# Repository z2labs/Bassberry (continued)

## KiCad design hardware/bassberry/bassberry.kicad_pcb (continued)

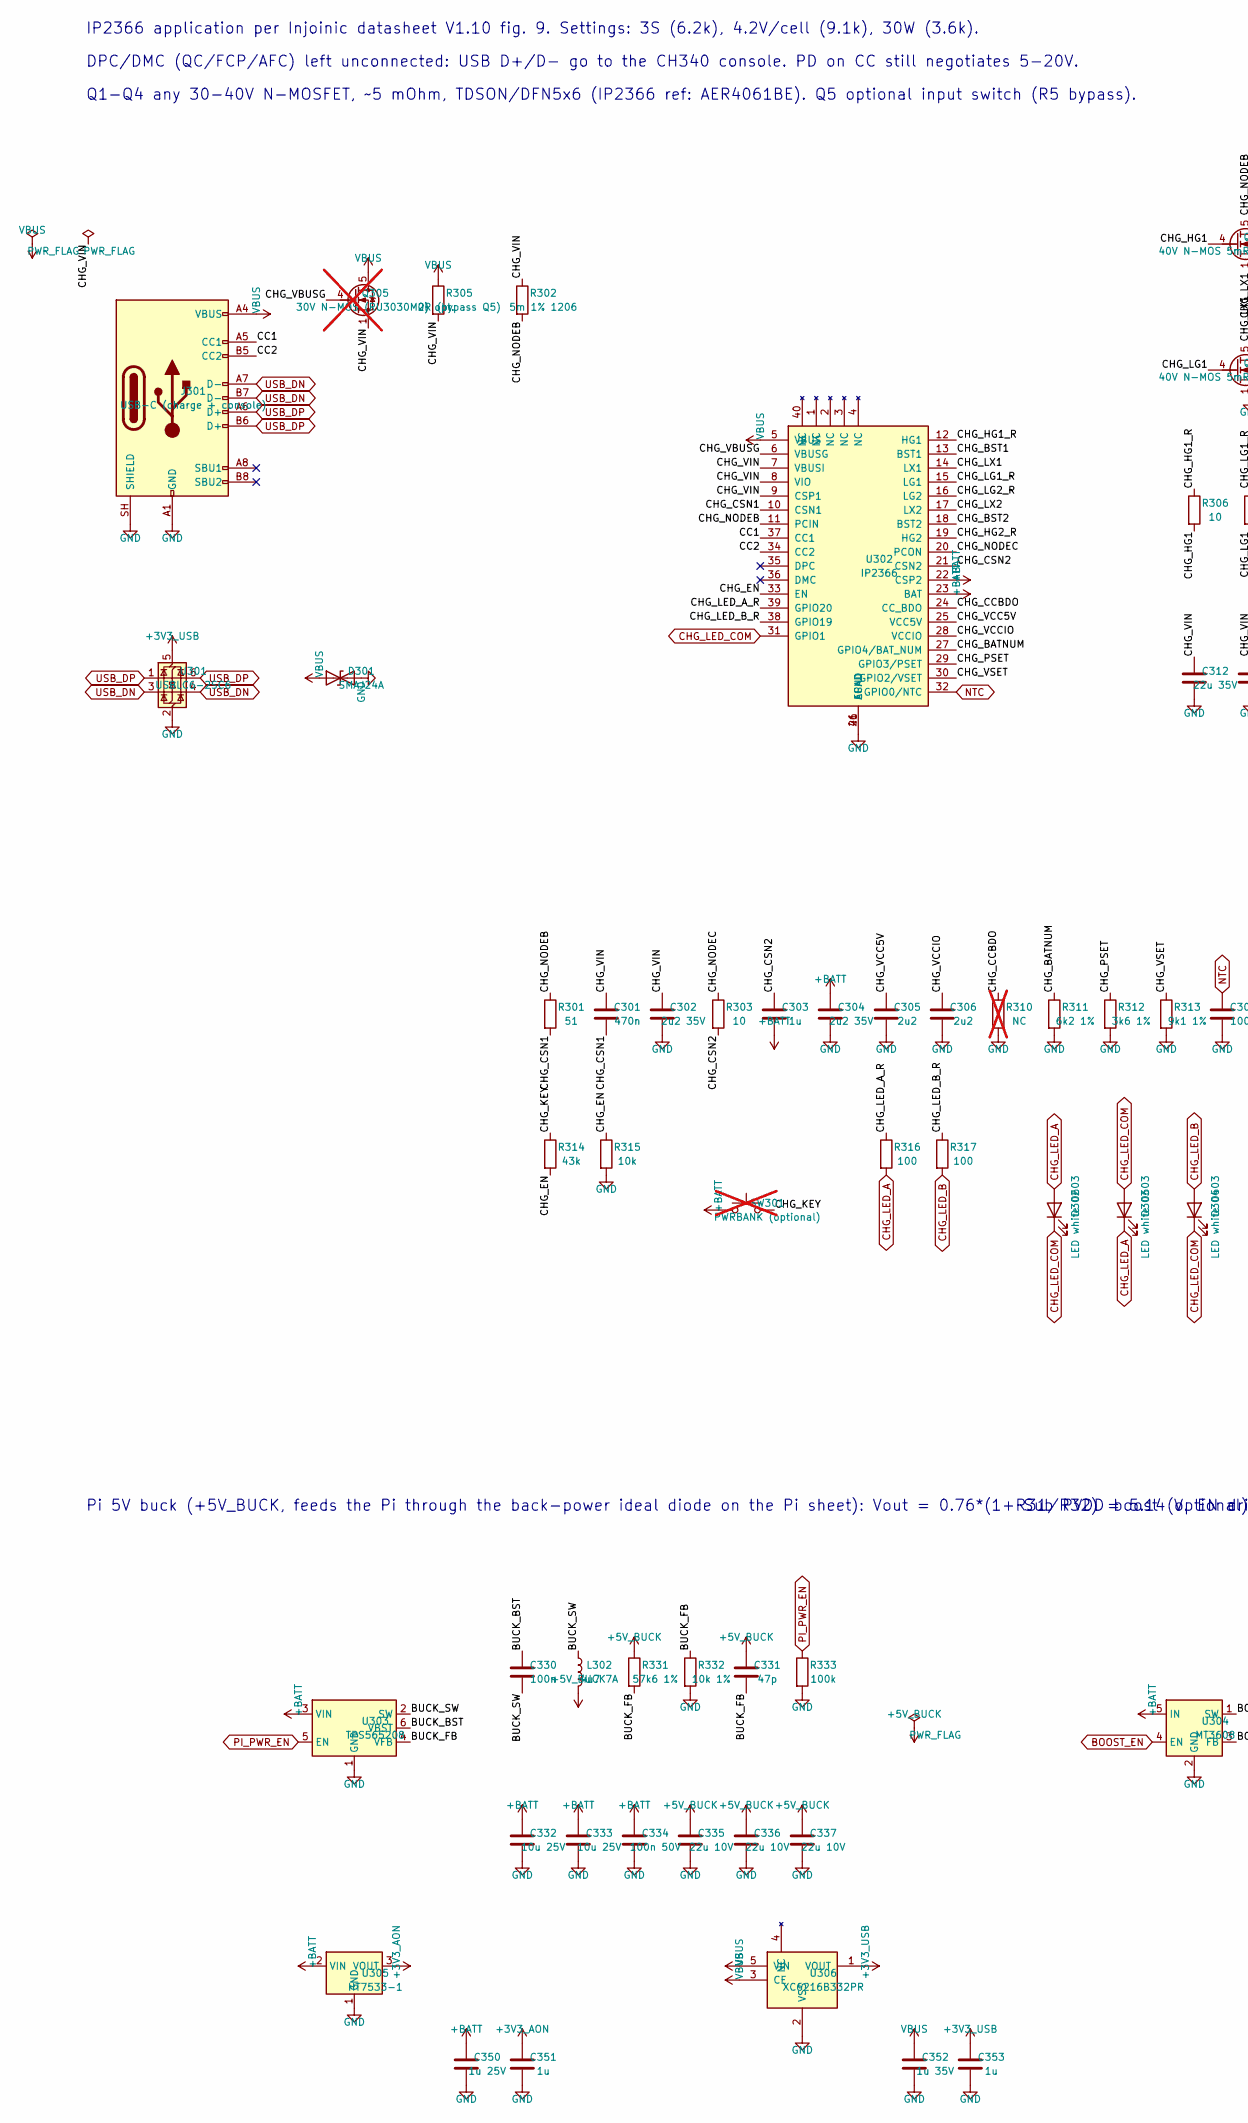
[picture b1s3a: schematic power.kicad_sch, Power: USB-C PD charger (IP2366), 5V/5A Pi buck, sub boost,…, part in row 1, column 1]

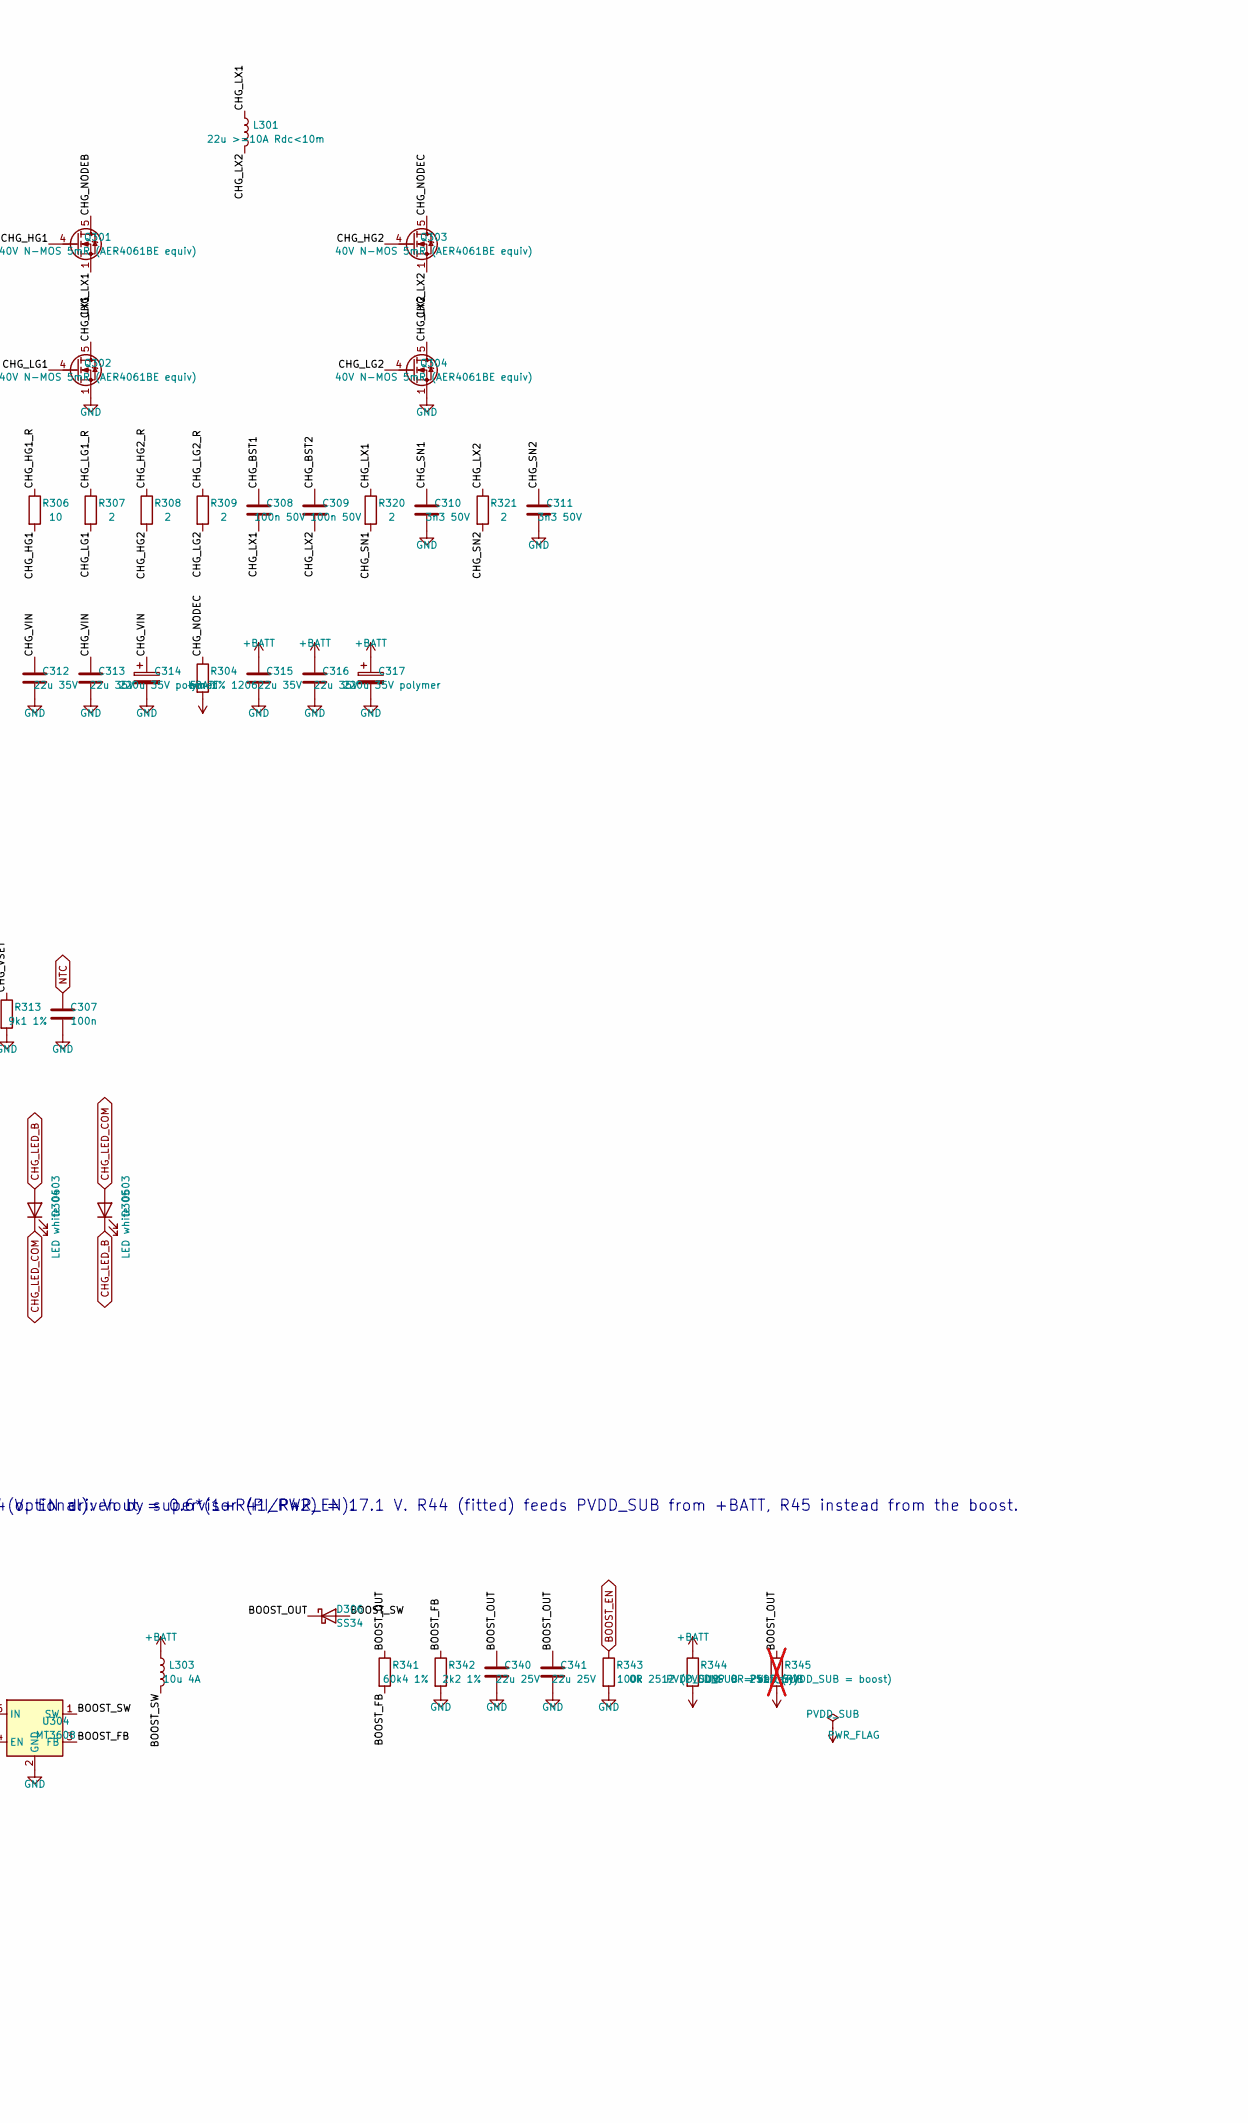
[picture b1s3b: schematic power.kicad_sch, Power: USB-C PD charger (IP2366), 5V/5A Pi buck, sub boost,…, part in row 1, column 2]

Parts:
C301: 470n; C_0603_1608Metric
C302, C304: 2u2 35V; C_0603_1608Metric
C303, C351, C353: 1u; C_0603_1608Metric
C305, C306: 2u2; C_0603_1608Metric
C307, C330: 100n; C_0603_1608Metric
C308, C309, C334: 100n 50V; C_0603_1608Metric
C310, C311: 3n3 50V; C_0603_1608Metric
C312, C313, C315, C316: 22u 35V; C_1210_3225Metric
C314, C317: 220u 35V polymer; CP_Elec_10x10.5
C331: 47p; C_0603_1608Metric
C332, C333: 10u 25V; C_1206_3216Metric
C335, C336, C337: 22u 10V; C_1206_3216Metric
C340, C341: 22u 25V; C_1210_3225Metric
C350: 1u 25V; C_0603_1608Metric
C352: 1u 35V; C_0603_1608Metric
D301: SMAJ24A; D_SMA
D302, D303, D304, D305: LED white 0603; LED_0603_1608Metric
D306: SS34; D_SMA
J301: USB-C (charge + console); USB_C_Receptacle_HRO_TYPE-C-31-M-12
L301: 22u >=10A Rdc<10m; L_Sunlord_MWSA1265S
L302: 4u7 7A; L_Changjiang_FXL1040
L303: 10u 4A; L_Changjiang_FXL1040
Q301, Q302, Q303, Q304: 40V N-MOS 5mR (AER4061BE equiv); TDSON-8-1
Q305: 30V N-MOS (RU3030M2) opt.; TDSON-8-1; not fitted
R301: 51; R_0603_1608Metric
R302, R304: 5m 1% 1206; R_1206_3216Metric
R303, R306: 10; R_0603_1608Metric
R305: 0R (bypass Q5); R_1206_3216Metric
R307, R308, R309, R320, R321: 2; R_0603_1608Metric
R310: NC; R_0603_1608Metric; not fitted
R311: 6k2 1%; R_0603_1608Metric
R312: 3k6 1%; R_0603_1608Metric
R313: 9k1 1%; R_0603_1608Metric
R314: 43k; R_0603_1608Metric
R315: 10k; R_0603_1608Metric
R316, R317: 100; R_0603_1608Metric
R331: 57k6 1%; R_0603_1608Metric
R332: 10k 1%; R_0603_1608Metric
R333, R343: 100k; R_0603_1608Metric
R341: 60k4 1%; R_0603_1608Metric
R342: 2k2 1%; R_0603_1608Metric
R344: 0R 2512 (PVDD_SUB = battery); R_2512_6332Metric
R345: DNP 0R 2512 (PVDD_SUB = boost); R_2512_6332Metric; not fitted
SW301: PWRBANK (optional); SW_SPST_TL3342; not fitted
U301: USBLC6-2SC6; SOT-23-6
U302: IP2366; QFN-40-1EP_5x5mm_P0.4mm_EP3.6x3.6mm_ThermalVias
U303: TPS565208; SOT-23-6
U304: MT3608; SOT-23-6
U305: HT7533-1; SOT-89-3
U306: XC6216B332PR; SOT-89-5

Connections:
+3V3_AON: C351.1, U305.3 (VOUT); also elsewhere on the board
+3V3_USB: C353.1, U301.5 (VBUS), U306.1 (VOUT); also elsewhere on the board
+5V_BUCK: C331.1, C335.1, C336.1, C337.1, L302.2, R331.1; also elsewhere on the board
+BATT: C303.2, C304.1, C315.1, C316.1, C317.1, C332.1, C333.1, C334.1, C350.1, L303.1, R304.2, R344.1, SW301.1, U302.22 (CSP2), U302.23 (BAT), U303.3 (VIN), U304.5 (IN), U305.2 (VIN); also elsewhere on the board
/power/BOOST_FB: R341.2, R342.1, U304.3 (FB)
/power/BOOST_OUT: C340.1, C341.1, D306.1 (K), R341.1, R345.1
/power/BOOST_SW: D306.2 (A), L303.2, U304.1 (SW)
/power/BUCK_BST: C330.1, U303.6 (VBST)
/power/BUCK_FB: C331.2, R331.2, R332.1, U303.4 (VFB)
/power/BUCK_SW: C330.2, L302.1, U303.2 (SW)
/power/CC1: J301.A5 (CC1), U302.37 (CC1)
/power/CC2: J301.B5 (CC2), U302.34 (CC2)
/power/CHG_BATNUM: R311.1, U302.27 (GPIO4/BAT_NUM)
/power/CHG_BST1: C308.1, U302.13 (BST1)
/power/CHG_BST2: C309.1, U302.18 (BST2)
/power/CHG_CCBDO: R310.1, U302.24 (CC_BDO)
/power/CHG_CSN1: C301.2, R301.2, U302.10 (CSN1)
/power/CHG_CSN2: C303.1, R303.2, U302.21 (CSN2)
/power/CHG_EN: R314.2, R315.1, U302.33 (EN)
/power/CHG_HG1: Q301.4 (G), R306.2
/power/CHG_HG1_R: R306.1, U302.12 (HG1)
/power/CHG_HG2: Q303.4 (G), R308.2
/power/CHG_HG2_R: R308.1, U302.19 (HG2)
/power/CHG_KEY: R314.1, SW301.2
/power/CHG_LED_A_R: R316.1, U302.39 (GPIO20)
/power/CHG_LED_B_R: R317.1, U302.38 (GPIO19)
/power/CHG_LG1: Q302.4 (G), R307.2
/power/CHG_LG1_R: R307.1, U302.15 (LG1)
/power/CHG_LG2: Q304.4 (G), R309.2
/power/CHG_LG2_R: R309.1, U302.16 (LG2)
/power/CHG_LX1: C308.2, L301.1, Q301.1 (S), Q301.2 (S), Q301.3 (S), Q302.5 (D), R320.1, U302.14 (LX1)
/power/CHG_LX2: C309.2, L301.2, Q303.1 (S), Q303.2 (S), Q303.3 (S), Q304.5 (D), R321.1, U302.17 (LX2)
/power/CHG_NODEB: Q301.5 (D), R301.1, R302.2, U302.11 (PCIN)
/power/CHG_NODEC: Q303.5 (D), R303.1, R304.1, U302.20 (PCON)
/power/CHG_PSET: R312.1, U302.29 (GPIO3/PSET)
/power/CHG_SN1: C310.1, R320.2
/power/CHG_SN2: C311.1, R321.2
/power/CHG_VBUSG: Q305.4 (G), U302.6 (VBUSG)
/power/CHG_VCC5V: C305.1, U302.25 (VCC5V)
/power/CHG_VCCIO: C306.1, U302.28 (VCCIO)
/power/CHG_VIN: C301.1, C302.1, C312.1, C313.1, C314.1, Q305.1 (S), Q305.2 (S), Q305.3 (S), R302.1, R305.2, U302.7 (VBUSI), U302.8 (VIO), U302.9 (CSP1)
/power/CHG_VSET: R313.1, U302.30 (GPIO2/VSET)
BOOST_EN: R343.1, U304.4 (EN); also elsewhere on the board
CHG_LED_A: D302.2 (A), D303.1 (K), R316.2
CHG_LED_B: D304.2 (A), D305.1 (K), R317.2
CHG_LED_COM: D302.1 (K), D303.2 (A), D304.1 (K), D305.2 (A), U302.31 (GPIO1)
GND: C302.2, C304.2, C305.2, C306.2, C307.2, C310.2, C311.2, C312.2, C313.2, C314.2, C315.2, C316.2, C317.2, C332.2, C333.2, C334.2, C335.2, C336.2, C337.2, C340.2, C341.2, C350.2, C351.2, C352.2, C353.2, D301.2 (A2), J301.A1 (GND), J301.A12 (GND), J301.B1 (GND), J301.B12 (GND), J301.SH (SHIELD), Q302.1 (S), Q302.2 (S), Q302.3 (S), Q304.1 (S), Q304.2 (S), Q304.3 (S), R310.2, R311.2, R312.2, R313.2, R315.2, R332.2, R333.2, R342.2, R343.2, U301.2 (GND), U302.26 (AGND), U302.41 (EPAD), U303.1 (GND), U304.2 (GND), U305.1 (GND), U306.2 (VSS); also elsewhere on the board
NTC: C307.1, U302.32 (GPIO0/NTC); also elsewhere on the board
PI_PWR_EN: R333.1, U303.5 (EN); also elsewhere on the board
PVDD_SUB: R344.2, R345.2; also elsewhere on the board
USB_DN: J301.A7 (D-), J301.B7 (D-), U301.3 (I/O2), U301.4 (I/O2); also elsewhere on the board
USB_DP: J301.A6 (D+), J301.B6 (D+), U301.1 (I/O1), U301.6 (I/O1); also elsewhere on the board
VBUS: C352.1, D301.1 (A1), J301.A4 (VBUS), J301.A9 (VBUS), J301.B4 (VBUS), J301.B9 (VBUS), Q305.5 (D), R305.1, U302.5 (VBUS), U306.3 (CE), U306.5 (VIN)

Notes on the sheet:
IP2366 application per Injoinic datasheet V1.10 fig. 9. Settings: 3S (6.2k), 4.2V/cell (9.1k), 30W (3.6k).
DPC/DMC (QC/FCP/AFC) left unconnected: USB D+/D- go to the CH340 console. PD on CC still negotiates 5-20V.
Q1-Q4 any 30-40V N-MOSFET, ~5 mOhm, TDSON/DFN5x6 (IP2366 ref: AER4061BE). Q5 optional input switch (R5 bypass).
Pi 5V buck (+5V_BUCK, feeds the Pi through the back-power ideal diode on the Pi sheet): Vout = 0.76*(1+R31/R32) = 5.14 V. EN driven by supervisor (PI_PWR_EN).
Sub PVDD boost (optional): Vout = 0.6*(1+R41/R42) = 17.1 V. R44 (fitted) feeds PVDD_SUB from +BATT, R45 instead from the boost.

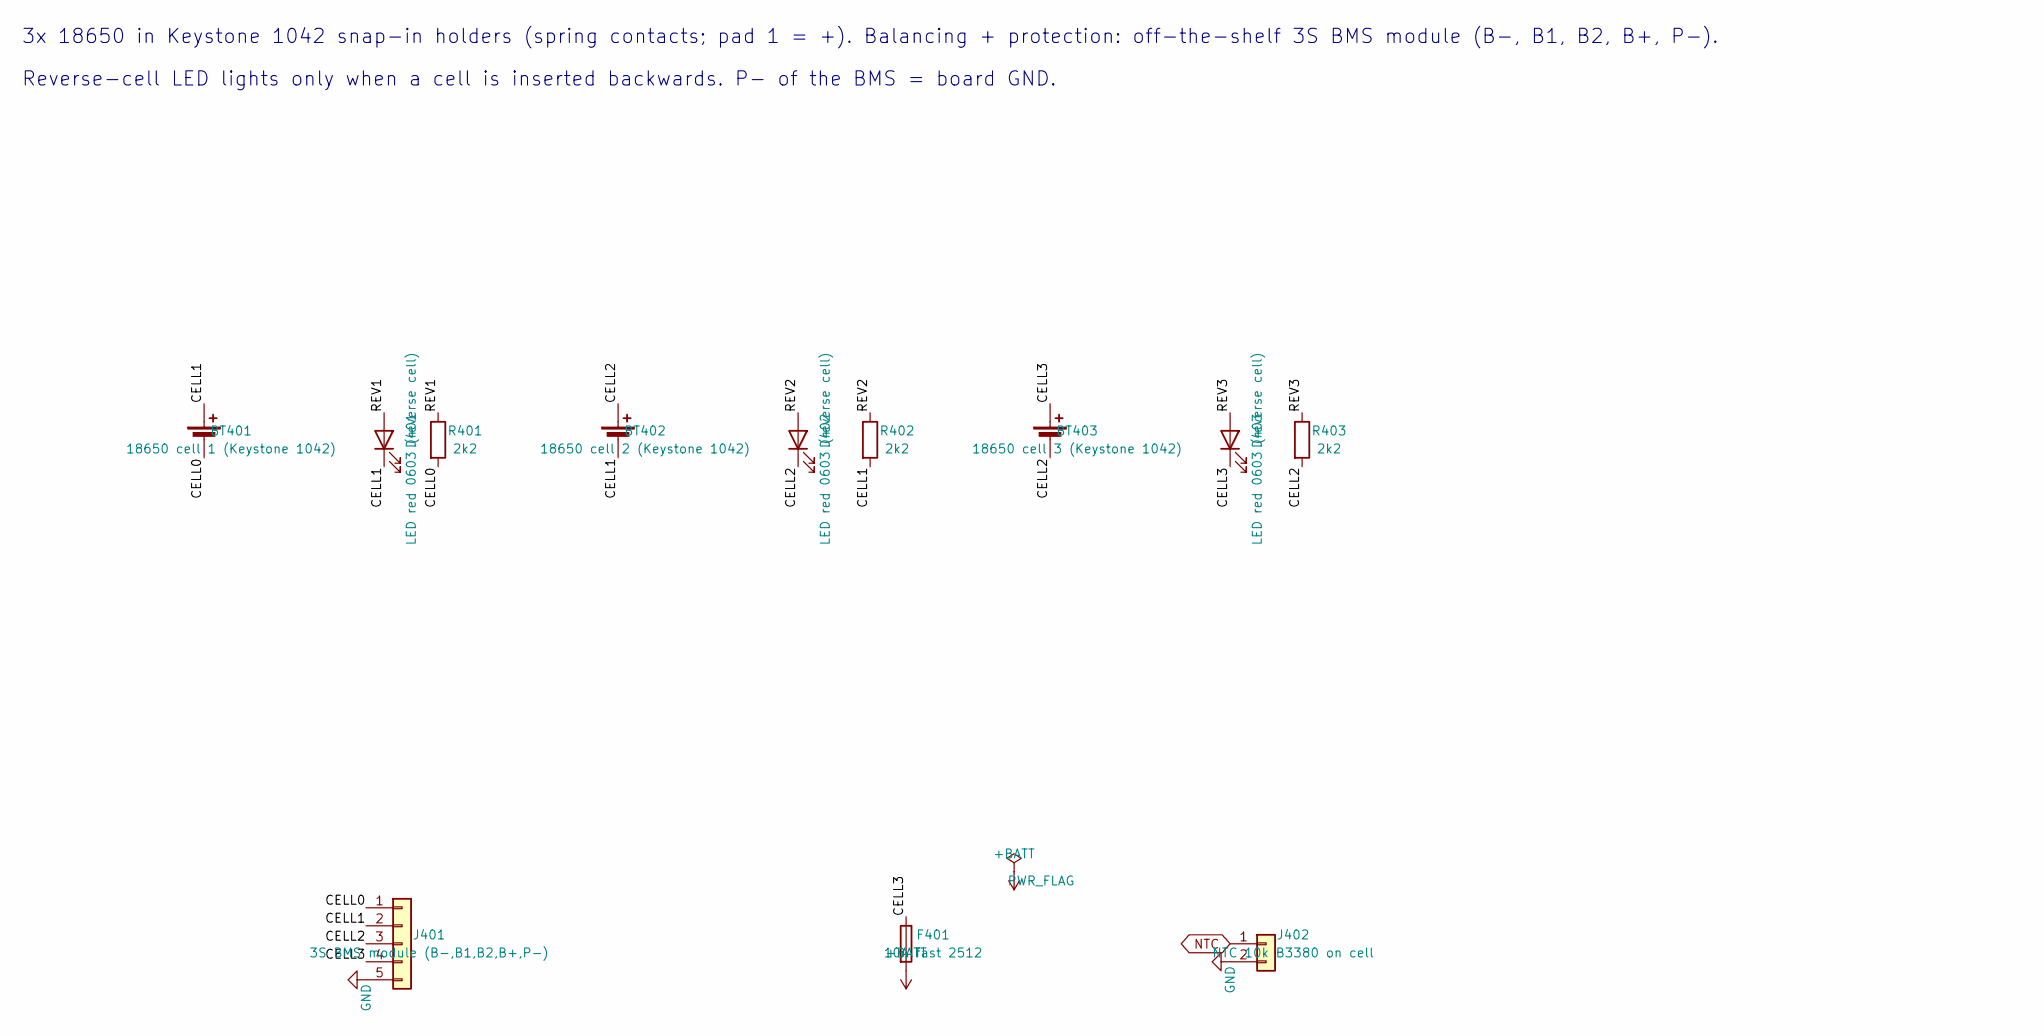
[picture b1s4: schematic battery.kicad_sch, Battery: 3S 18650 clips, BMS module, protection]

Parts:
BT401: 18650 cell 1 (Keystone 1042); BatteryHolder_Keystone_1042_1x18650
BT402: 18650 cell 2 (Keystone 1042); BatteryHolder_Keystone_1042_1x18650
BT403: 18650 cell 3 (Keystone 1042); BatteryHolder_Keystone_1042_1x18650
D401, D402, D403: LED red 0603 (reverse cell); LED_0603_1608Metric
F401: 10A fast 2512; Fuse_2512_6332Metric
J401: 3S BMS module (B-,B1,B2,B+,P-); SolderWire-1sqmm_1x05_P5.4mm_D1.4mm_OD2.7mm
J402: NTC 10k B3380 on cell; JST_PH_B2B-PH-K_1x02_P2.00mm_Vertical
R401, R402, R403: 2k2; R_0603_1608Metric

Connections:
+BATT: F401.2; also elsewhere on the board
/battery/CELL0: BT401.2 (-), J401.1, R401.2
/battery/CELL1: BT401.1 (+), BT402.2 (-), D401.1 (K), J401.2, R402.2
/battery/CELL2: BT402.1 (+), BT403.2 (-), D402.1 (K), J401.3, R403.2
/battery/CELL3: BT403.1 (+), D403.1 (K), F401.1, J401.4
/battery/REV1: D401.2 (A), R401.1
/battery/REV2: D402.2 (A), R402.1
/battery/REV3: D403.2 (A), R403.1
GND: J401.5, J402.2; also elsewhere on the board
NTC: J402.1; also elsewhere on the board

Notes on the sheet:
3x 18650 in Keystone 1042 snap-in holders (spring contacts; pad 1 = +). Balancing + protection: off-the-shelf 3S BMS module (B-, B1, B2, B+, P-).
Reverse-cell LED lights only when a cell is inserted backwards. P- of the BMS = board GND.

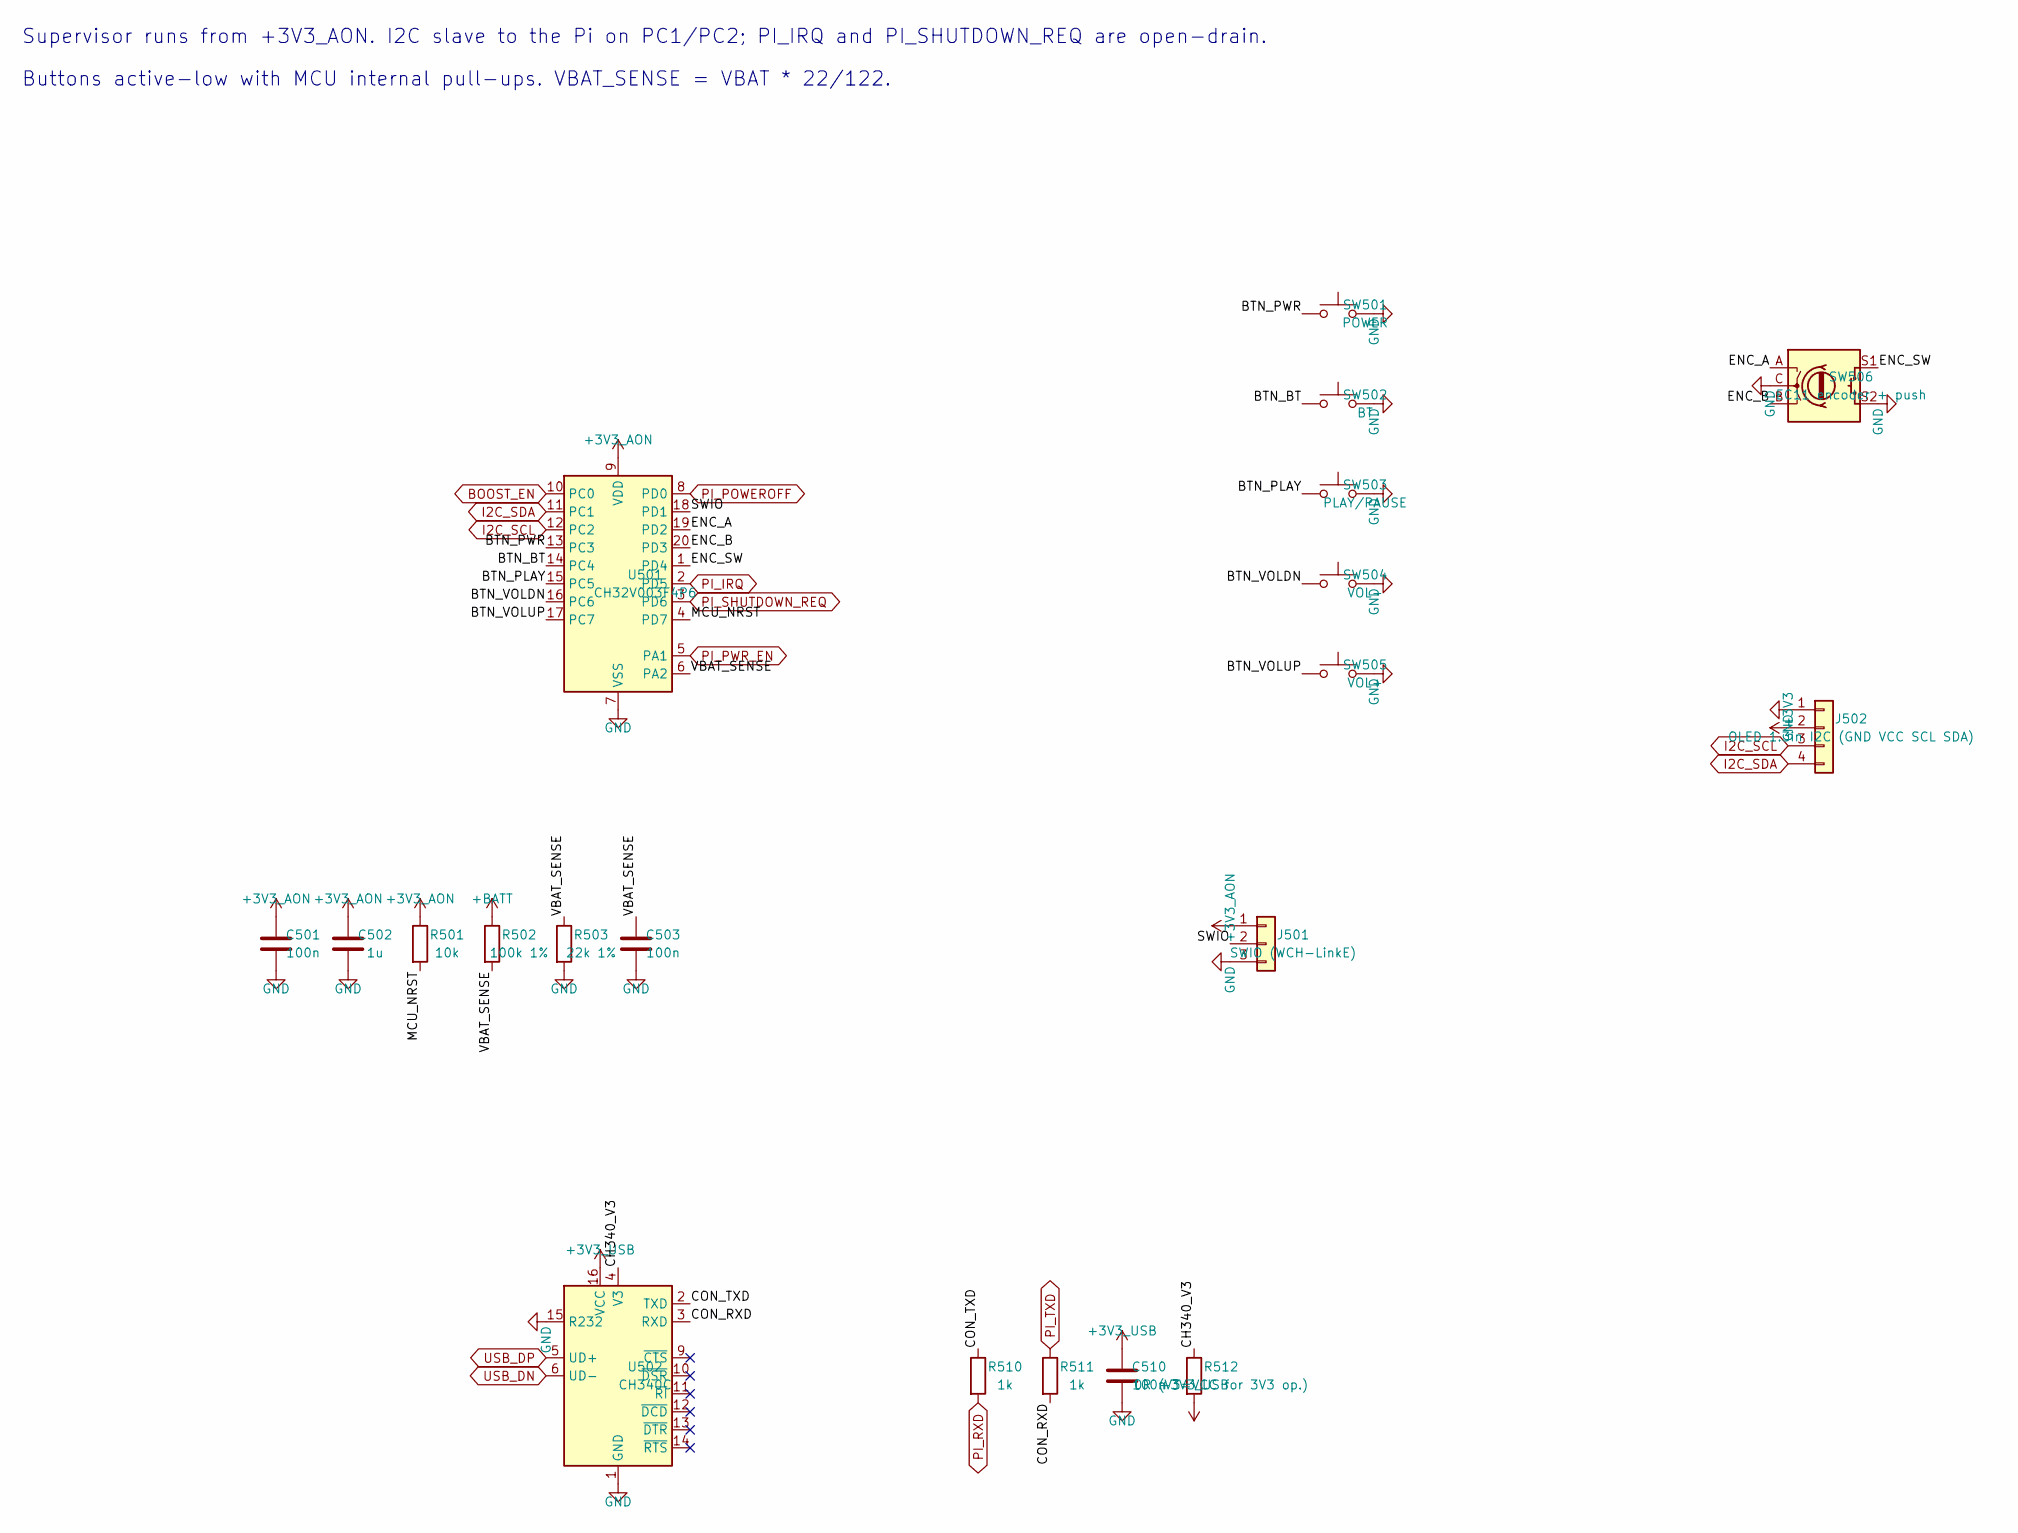
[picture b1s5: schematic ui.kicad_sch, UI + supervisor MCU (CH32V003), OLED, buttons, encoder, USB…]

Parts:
C501, C503, C510: 100n; C_0603_1608Metric
C502: 1u; C_0603_1608Metric
J501: SWIO (WCH-LinkE); PinHeader_1x03_P2.54mm_Vertical
J502: OLED 1.3in I2C (GND VCC SCL SDA); PinSocket_1x04_P2.54mm_Horizontal
R501: 10k; R_0603_1608Metric
R502: 100k 1%; R_0603_1608Metric
R503: 22k 1%; R_0603_1608Metric
R510, R511: 1k; R_0603_1608Metric
R512: 0R (V3=VCC for 3V3 op.); R_0603_1608Metric
SW501: POWER; SW_SPST_TL3342
SW502: BT; SW_SPST_TL3342
SW503: PLAY/PAUSE; SW_SPST_TL3342
SW504: VOL-; SW_SPST_TL3342
SW505: VOL+; SW_SPST_TL3342
SW506: EC11 encoder + push; RotaryEncoder_Alps_EC11E-Switch_Vertical_H20mm
U501: CH32V003F4P6; TSSOP-20_4.4x6.5mm_P0.65mm
U502: CH340C; SOIC-16_3.9x9.9mm_P1.27mm

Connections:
+3V3: J502.2; also elsewhere on the board
+3V3_AON: C501.1, C502.1, J501.1, R501.1, U501.9 (VDD); also elsewhere on the board
+3V3_USB: C510.1, R512.2, U502.16 (VCC); also elsewhere on the board
+BATT: R502.1; also elsewhere on the board
/ui/BTN_BT: SW502.1, U501.14 (PC4)
/ui/BTN_PLAY: SW503.1, U501.15 (PC5)
/ui/BTN_PWR: SW501.1, U501.13 (PC3)
/ui/BTN_VOLDN: SW504.1, U501.16 (PC6)
/ui/BTN_VOLUP: SW505.1, U501.17 (PC7)
/ui/CH340_V3: R512.1, U502.4 (V3)
/ui/CON_RXD: R511.2, U502.3 (RXD)
/ui/CON_TXD: R510.1, U502.2 (TXD)
/ui/ENC_A: SW506.A, U501.19 (PD2)
/ui/ENC_B: SW506.B, U501.20 (PD3)
/ui/ENC_SW: SW506.S1, U501.1 (PD4)
/ui/MCU_NRST: R501.2, U501.4 (PD7)
/ui/SWIO: J501.2, U501.18 (PD1)
/ui/VBAT_SENSE: C503.1, R502.2, R503.1, U501.6 (PA2)
BOOST_EN: U501.10 (PC0); also elsewhere on the board
GND: C501.2, C502.2, C503.2, C510.2, J501.3, J502.1, R503.2, SW501.2, SW502.2, SW503.2, SW504.2, SW505.2, SW506.C, SW506.S2, U501.7 (VSS), U502.1 (GND), U502.15 (R232); also elsewhere on the board
I2C_SCL: J502.3, U501.12 (PC2); also elsewhere on the board
I2C_SDA: J502.4, U501.11 (PC1); also elsewhere on the board
PI_IRQ: U501.2 (PD5); also elsewhere on the board
PI_POWEROFF: U501.8 (PD0); also elsewhere on the board
PI_PWR_EN: U501.5 (PA1); also elsewhere on the board
PI_RXD: R510.2; also elsewhere on the board
PI_SHUTDOWN_REQ: U501.3 (PD6); also elsewhere on the board
PI_TXD: R511.1; also elsewhere on the board
USB_DN: U502.6 (UD-); also elsewhere on the board
USB_DP: U502.5 (UD+); also elsewhere on the board

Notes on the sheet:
Supervisor runs from +3V3_AON. I2C slave to the Pi on PC1/PC2; PI_IRQ and PI_SHUTDOWN_REQ are open-drain.
Buttons active-low with MCU internal pull-ups. VBAT_SENSE = VBAT * 22/122.

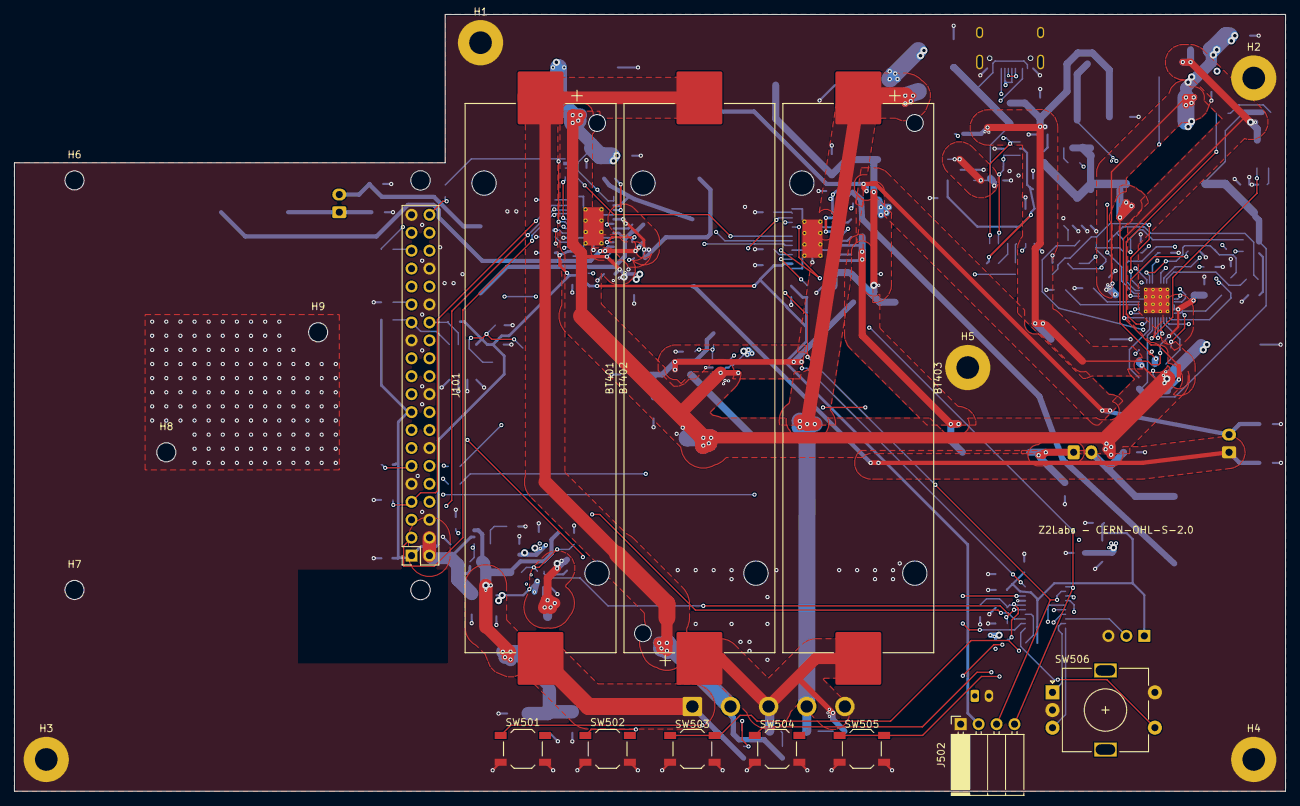
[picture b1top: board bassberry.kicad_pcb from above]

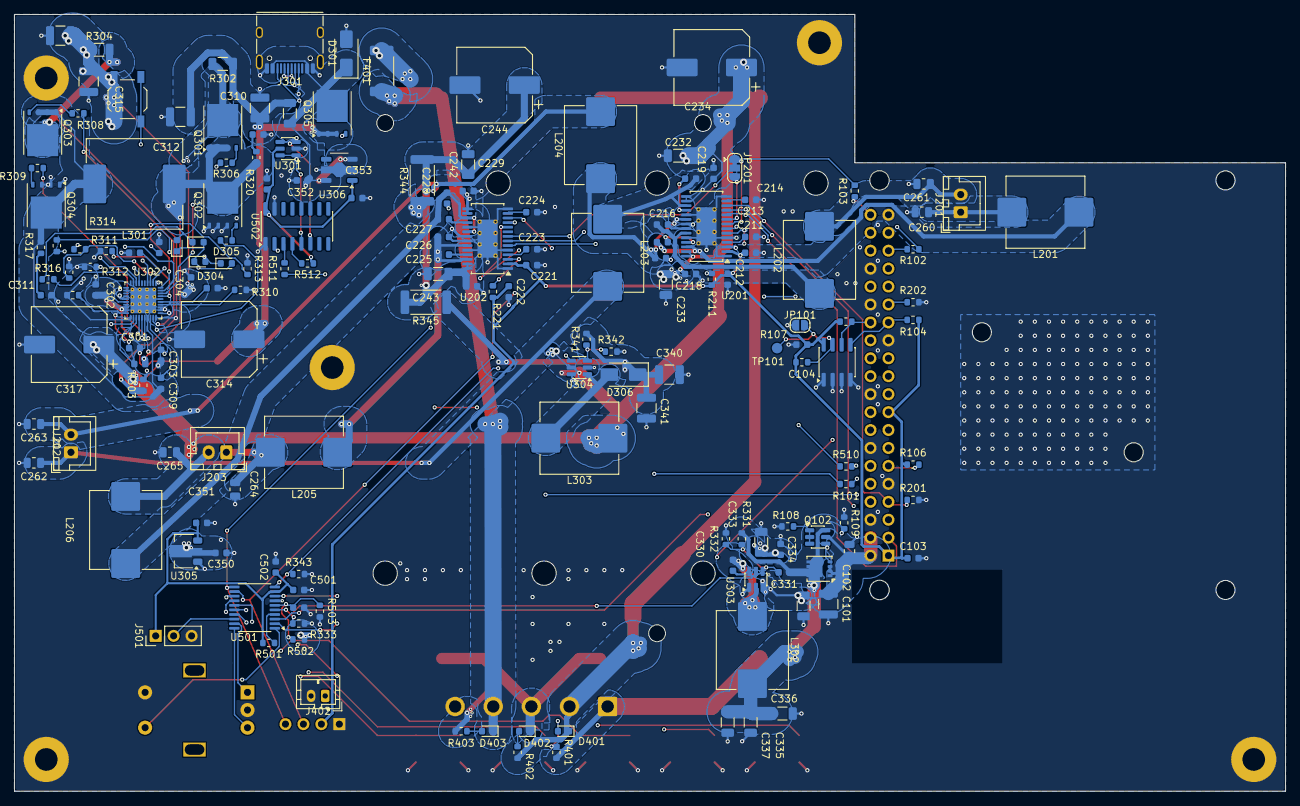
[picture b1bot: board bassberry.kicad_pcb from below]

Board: 4 copper layers, 180.0 x 110.0 mm, 188 parts (168 on the bottom side), 124 nets.

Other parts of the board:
H1, H2, H3, H4, H5: MountingHole_3.2mm_M3_Pad
H6, H7, H8, H9: MountingHole_2.7mm_M2.5

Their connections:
GND: H1.1, H2.1, H3.1, H4.1, H5.1; also elsewhere on the board

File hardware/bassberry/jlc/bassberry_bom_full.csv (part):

Qty,Comment,Designator,Footprint,LCSC Part #,MPN,Manufacturer,Basic/Extended,SMT/THT,Key spec,Checked at,Notes
1,18650 cell 1 (Keystone 1042),BT401,BatteryHolder_Keystone_1042_1x18650,C5249310,1042,Keystone,Extended,SMT-tab part; JLC lists assembly type 'Wave Soldering' (likely manual/hand-solder step),"1x18650 holder, SMD solder tabs",https://jlcpcb.com/partdetail/C5249310,Exact part at LCSC. Large holder: confirm with JLC whether they place it or hand-solder; check stock (often low).
1,18650 cell 2 (Keystone 1042),BT402,BatteryHolder_Keystone_1042_1x18650,C5249310,1042,Keystone,Extended,SMT-tab part; JLC lists assembly type 'Wave Soldering',1x18650 holder,https://jlcpcb.com/partdetail/C5249310,Same as BT401.
1,18650 cell 3 (Keystone 1042),BT403,BatteryHolder_Keystone_1042_1x18650,C5249310,1042,Keystone,Extended,SMT-tab part; JLC lists assembly type 'Wave Soldering',1x18650 holder,https://jlcpcb.com/partdetail/C5249310,Same as BT401.
1,100u 6.3V,C101,C_1210_3225Metric,C49066,CL32A107MQVNNNE,Samsung Electro-Mechanics,Extended,SMT,100uF 6.3V X5R 20%,https://jlcpcb.com/partdetail/C49066,LCSC stock 126002. Basic C15008 is 1206 (does not match 1210 footprint)
1,10u,C102,C_0805_2012Metric,C15850,CL21A106KAYNNNE,Samsung Electro-Mechanics,Basic,SMT,10uF 25V X5R 10%,https://jlcpcb.com/partdetail/C15850,
9,100n,"C103,C104,C212,C222,C307,C330,C501,C503,C510",C_0603_1608Metric,C14663,CC0603KRX7R9BB104,YAGEO,Basic,SMT,100nF 50V X7R 10%,https://jlcpcb.com/partdetail/C14663,
2,4u7,"C211,C221",C_0603_1608Metric,C19666,CL10A475KO8NNNC,Samsung Electro-Mechanics,Basic,SMT,4.7uF 16V X5R 10%,https://jlcpcb.com/partdetail/C19666,
8,1u,"C213,C214,C223,C224,C303,C351,C353,C502",C_0603_1608Metric,C15849,CL10A105KB8NNNC,Samsung Electro-Mechanics,Basic,SMT,1uF 50V X5R 10%,https://jlcpcb.com/partdetail/C15849,
8,220n,"C215,C216,C217,C218,C225,C226,C227,C228",C_0603_1608Metric,C21120,CL10B224KA8NNNC,Samsung Electro-Mechanics,Basic,SMT,220nF 25V X7R 10%,https://jlcpcb.com/partdetail/C21120,
7,100n 50V,"C219,C229,C231,C241,C308,C309,C334",C_0603_1608Metric,C14663,CC0603KRX7R9BB104,YAGEO,Basic,SMT,100nF 50V X7R 10%,https://jlcpcb.com/partdetail/C14663,Same part as plain 100n line
4,22u 25V,"C232,C233,C242,C243",C_1206_3216Metric,C12891,CL31A226KAHNNNE,Samsung Electro-Mechanics,Basic,SMT,22uF 25V X5R 10%,https://jlcpcb.com/partdetail/C12891,"Rated exactly 25V; heavy DC-bias derating (1206 X5R, expect well under half of 22uF at 12-20V)"
2,470u 25V low-ESR,"C234,C244",CP_Elec_10x10.5,C248607,EEEFK1E471P,Panasonic,Extended,SMT,470uF 25V Al electrolytic FK low-impedance series; 105C 2000h,https://jlcpcb.com/partdetail/C248607,"LCSC stock 7217. ESR not listed on page (FK series is Panasonic's low-Z line, check datasheet if ripple critical). Hybrid-polymer alt: Rubycon 25PJV470MSPA10X10.5 C239327 (2315 pcs)"
6,680n 50V,"C260,C261,C262,C263,C264,C265",C_0805_2012Metric,C472832,CL21B684KBFVPNE,Samsung Electro-Mechanics,Extended,SMT,680nF 50V X7R 10%,https://jlcpcb.com/partdetail/C472832,LCSC stock 5075 (enough for 6/board but modest for volume runs)
1,470n,C301,C_0603_1608Metric,C1623,CL10B474KA8NNNC,Samsung Electro-Mechanics,Basic,SMT,470nF 25V X7R 10%,https://jlcpcb.com/partdetail/C1623,
2,2u2 35V,"C302,C304",C_0603_1608Metric,C307463,CL10A225KL8NNNC,Samsung Electro-Mechanics,Extended,SMT,2.2uF 35V X5R 10%,https://jlcpcb.com/partdetail/C307463,LCSC stock 8750; no Basic 0603 2.2uF >=35V
2,2u2,"C305,C306",C_0603_1608Metric,C23630,CL10A225KO8NNNC,Samsung Electro-Mechanics,Basic,SMT,2.2uF 16V X5R 10%,https://jlcpcb.com/partdetail/C23630,
2,3n3 50V,"C310,C311",C_0603_1608Metric,C152910,0603N332J500CT,Walsin,Extended,SMT,3.3nF 50V NP0/C0G 5%,https://jlcpcb.com/partdetail/C152910,LCSC stock 62000. Basic C1613 is X7R (not C0G); Samsung CL10C332JB8NNNC C55395 is C0G but LCSC out of stock
4,22u 35V,"C312,C313,C315,C316",C_1210_3225Metric,C778721,GMK325BJ226MM-P,Taiyo Yuden,Extended,SMT,22uF 35V X5R 20%,https://jlcpcb.com/partdetail/C778721,LCSC stock 163870
2,220u 35V polymer,"C314,C317",CP_Elec_10x10.5,C278516,EEHZK1V331P,Panasonic,Extended,SMT,330uF 35V hybrid polymer Al; ESR 20mOhm,https://jlcpcb.com/partdetail/C278516,"Nearest STOCKED fit: 330uF instead of 220uF (LCSC 4869 pcs on 2026-10-27). Exact 220uF/35V EEHZA1V221P C454349 (D10xL10.2, ESR 20mOhm, 2.5A@100kHz) exists but LCSC shows Out of Stock; alt Rubycon 35PJV330M10X10.5 C3274921 (330uF 35V hybrid, 1000 pcs)"
1,47p,C331,C_0603_1608Metric,C1671,CL10C470JB8NNNC,Samsung Electro-Mechanics,Basic,SMT,47pF 50V C0G 5%,https://jlcpcb.com/partdetail/C1671,
2,10u 25V,"C332,C333",C_1206_3216Metric,C13585,CL31A106KBHNNNE,Samsung Electro-Mechanics,Basic,SMT,10uF 50V X5R 10%,https://jlcpcb.com/partdetail/C13585,50V rating covers 25V
3,22u 10V,"C335,C336,C337",C_1206_3216Metric,C12891,CL31A226KAHNNNE,Samsung Electro-Mechanics,Basic,SMT,22uF 25V X5R 10%,https://jlcpcb.com/partdetail/C12891,25V rating covers 10V
2,22u 25V,"C340,C341",C_1210_3225Metric,C52306,CL32A226KAJNNNE,Samsung Electro-Mechanics,Extended,SMT,22uF 25V X5R 10%,https://jlcpcb.com/partdetail/C52306,LCSC stock 153148; no Basic 1210 22uF
1,1u 25V,C350,C_0603_1608Metric,C15849,CL10A105KB8NNNC,Samsung Electro-Mechanics,Basic,SMT,1uF 50V X5R 10%,https://jlcpcb.com/partdetail/C15849,50V rating covers 25V
1,1u 35V,C352,C_0603_1608Metric,C15849,CL10A105KB8NNNC,Samsung Electro-Mechanics,Basic,SMT,1uF 50V X5R 10%,https://jlcpcb.com/partdetail/C15849,50V rating covers 35V
1,SMAJ24A,D301,D_SMA,C113962,SMAJ24A,MDD (Microdiode),Extended,SMT,"TVS uni, Vrwm 24V",https://jlcpcb.com/partdetail/C113962,"No Basic SMAJ24A found. Alternates (verified, Extended): C10769 RUILON, C3001960 UMW. Cathode band = pad 1 on D_SMA."
4,LED white 0603,"D302,D303,D304,D305",LED_0603_1608Metric,C2290,KT-0603W,Hubei KENTO,Basic,SMT,White,https://jlcpcb.com/partdetail/C2290,
1,SS34,D306,D_SMA,C8678,SS34,MDD (Microdiode),Basic,SMT,Schottky 40V 3A,https://jlcpcb.com/partdetail/C8678,
3,LED red 0603 (reverse cell),"D401,D402,D403",LED_0603_1608Metric,C2286,KT-0603R,Hubei KENTO,Basic,SMT,"Red, water-clear lens",https://jlcpcb.com/partdetail/C2286,Check polarity mark vs footprint pad 1 (cathode).
1,10A fast 2512,F401,Fuse_2512_6332Metric,C44479,0451010.MRL,Littelfuse,Extended,SMT,"10A 125VDC very fast-acting NANO2, IR 35/50A",https://jlcpcb.com/partdetail/C44479,No true 2512 (6332) 10A SMD fuse found at JLC/LCSC; nearest is 2410/6125 body - fits on 2512 pads in practice but better to change footprint to a 2410/NANO2 land pattern. LCSC stock ~28k. Note: 50A interrupt rating is low for a 3S 18650 pack short-circuit current
1,RPi 40-pin (face-down socket),J101,Raspberry_Pi_Zero_Socketed_THT_FaceDown_MountingHoles,C2977589,2.54-2*20,ZHOURI,Extended,THT,"2x20 female, 8.5 mm high",https://jlcpcb.com/partdetail/C2977589,Matches 8.5mm stacking height spec.
1,SAT LEFT,J201,JST_XH_B2B-XH-A_1x02_P2.50mm_Vertical,C158012,B2B-XH-A(LF)(SN),JST,Extended,THT,"2P 2.5mm vertical header, 3A",https://jlcpcb.com/partdetail/C158012,"Genuine JST. Alt verified: C2683608 (B2B-XH-A-MB2P-VH, JST)."
1,SAT RIGHT,J202,JST_XH_B2B-XH-A_1x02_P2.50mm_Vertical,C158012,B2B-XH-A(LF)(SN),JST,Extended,THT,2P 2.5mm vertical header,https://jlcpcb.com/partdetail/C158012,
1,SUB,J203,JST_XH_B2B-XH-A_1x02_P2.50mm_Vertical,C158012,B2B-XH-A(LF)(SN),JST,Extended,THT,2P 2.5mm vertical header,https://jlcpcb.com/partdetail/C158012,
1,USB-C (charge + console),J301,USB_C_Receptacle_HRO_TYPE-C-31-M-12,C165948,TYPE-C-31-M-12,Korean Hroparts (HRO),Extended,"SMT (shell legs THT, JLC handles as SMT part)",USB-C receptacle 16-pin,https://jlcpcb.com/partdetail/C165948,Exact part.
1,NTC 10k B3380 on cell,J402,JST_PH_B2B-PH-K_1x02_P2.00mm_Vertical,C131337,B2B-PH-K-S(LF)(SN),JST,Extended,THT,2P 2.0mm vertical header,https://jlcpcb.com/partdetail/C131337,Genuine JST; THT -> JLC THT/hand-solder service.
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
